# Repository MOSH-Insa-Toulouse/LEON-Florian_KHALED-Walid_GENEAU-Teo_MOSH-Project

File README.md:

___

# Keywords

___
> Arduino, Kicad, The Thing Networks, Lora, Node-Red, LT-spice  

___
# Membres du groupe

> Ce projet à été réalisé par : 
> - GENEAU Téo
> - KHALED Walid
> - LEON Florian
> 
___
# Description générale du projet 

Nous voulons dans ce projet réaliser un smart device, nous voulons récupérer les données d’un capteur de gaz et les envoyer via le protocole LORA sur le site TTN et ensuite afficher les données du capteur sur un Dashboard sur Node-Red. Nous nous intéressons aussi à la consommation d’Energie du capteur, donc nous allons utiliser le capteur sous un mode réveillé (très bref moment) pour mesurer et envoyer les données et un autre mode endormi où il ne consomme quasiment rien (pendant la majorité du temps).     

___
# Partie 1 : Conception du PCB 

Le Shield contient un circuit d’adaptation d’impédance pour relier le capteur de gaz au microcontrôleur (Arduino Uno) ainsi qu’un circuit d’interruption qui gère les deux mode «Sleep» et «Wake-up» du circuit et du capteur de gaz.

Un connecteur est prévu pour relier le circuit à l’antenne LORA. 

L’emplacement réservé au capteur de gaz est au milieu du PCB en forme de petits cercles. 

### **Schéma Kicad**

### **Visualisation du PCB** 

### **Visualisation du Shield en 3D** 

___
# Partie LT-SPICE 

Afin de simuler notre circuit d’interruption et gérer la consommation d’Energie du circuit nous avons utilisé LT-SPICE afin de simuler le comportement que nous désirons. 

Nous remarquons sur les deux figures suivantes qu’en variant les paramètres des différents composants du circuit notamment les résistances, nous parvenons à contrôler la durée d’interruption. 

___
# Partie Arduino 

Nous utilisons l’Arduino UNO comme microcontrôleur accompagné d’une breadboard pour monter le circuit prototype (circuit d’interruption + capteur de gaz groove + Antenne LORA). 

> Le code Arduino est composé des parties suivantes : 
>
> - Une partie d’acquisition des données du capteur et affichage sur moniteur série  
> - Une partie de configuration de la connexion TTN – LORA 
> - Une partie de gestion des deux modes Sleep et Wake-Up 

### **Affichage des données sur TTN** 

Les données sont envoyées sur le site TTN via LORA. 

Le code suivant nous permet de décoder les valeurs en hexadécimal reçues : 
```javascript
function decodeUplink(input) {
var data = input.bytes[0] << 8  | input.bytes[1];
  return {
    data: {
      gazValue: data/100
    },
    warnings: [],
    errors: []
  };
}
```

### **Partie consommation Energie**

Dans le but de diminuer au maximum la consommation d’Energie de notre système, nous avons utilisé un circuit d’interruption, nous arrivons même à éteindre et à rallumer le capteur avec ce circuit en rajoutant un transistor ce qui réduit énormément la consommation d’Energie du circuit car c’est le capteur qui consomme la quasi-totalité de l’Energie consommée par tout le circuit.

Ainsi, nous avons mis en place deux types d’interruption pour optimiser la consommation de notre circuit : une interruption matérielle et logicielle.

Notre interruption matérielle consiste en un déclenchement cyclique externe.

Pour cela, nous avons utilisé un AOP pour faire un comparateur, le circuit permet de généré des ondes carrées bases fréquences et de créer un circuit oscillateur permettant de faire varier la tension entre 0 et 5V de manière cyclique. Il est possible de modifier la fréquence en modifiant les valeurs de la capacité ou bien des résistances. En effet, si on augmente par exemple la valeur de la capacité, la fréquence diminuera et inversement. 

Nous avons simulé le circuit sur LT-Spice pour le choix des valeurs des résistances et de la capacité afin d’obtenir des périodes d’activités et d’inactivités adaptées à notre application.

L’interruption logicielle est réalisée par le code présent sur la carte. On réalise une interruption logicielle lorsque le circuit est dans une période inactive pour activer ou désactiver le capteur de gaz.

<ins>*Schéma du montage pour l’interruption logicielle (ici une LED à la place du capteur de gaz)*</ins>

Les figures suivantes montrent le comportement du système : 

L’interruption est annulée et le capteur se réveil «Wake-Up» prend la mesure et l’envoie (3 envoies pour éviter une potentiel perte du message) et se remet en mode «Sleep» pour s’en dormir. 

> «Dodo» (le capteur retourne au mode Sleep)
> 0 V en sortie de l’AOP 

> Mode Wake-Up et envoie de 3 messages (données)  
> 5 V en sortie de l’AOP

### **Bilan de puissance consommée**
Nous avons mesuré le courant en sortie du circuit, pour cela nous avons utilisé un détecteur d’intensité USB

<p style="text-align:center;"><ins><em>Détecteur de tension/intensité USB</em></ins></p>

Il permet de réaliser des mesures de courant consommé sur un port USB et ce en temps réel. Nous avons alors pu établir un tableau de mesures.

> Pour cela, nous avons mesurer la consommation en courant du circuit en fonction de son comportement :
> - En mode wake-up (actif), lorsque le circuit d’oscillation impose une tension à 5V.
> - En mode sleep, lorsque le circuit d’oscillation impose une tension à 0V et que le capteur de gaz est activé.
> - En mode sleep, lorsque le circuit d’oscillation impose une tension à 0V et que le capteur de gaz est désactivé par interruption logicielle.

Nous pouvons observer que c’est l’interruption matérielle qui a le plus d’impact sur la consommation, en effet, on passe de **0.22 à 0.04** A lors des périodes de sleep imposées par l’AOP comparateur, soit une réduction de **0.18 A**. Tandis que, l’interruption logicielle, elle, permet une économie de **0.16 A** en passant de **0.22 A à 0.06 A**, cette interruption permet de ne plus alimenter le capteur lors de la phase active, on peut alors remarquer que c’est le capteur de gaz qui consomme le plus dans le circuit avec une consommation correspond au **0.16 A** de différence. 

De plus, on a mesuré la durée des périodes de sleep et de wake-up du circuit, on observe une période moyenne de **123 secondes** pour les périodes inactives du circuit contre 17 secondes en moyenne pour la phase active, or, l’interruption logicielle active le capteur que pour une durée de **7 secondes**.

On convertit en heure et on multiplie par les valeurs de courant correspondantes mesurées pour obtenir la mesure en Ah, puis on multiplie par le voltage (5V) pour obtenir une mesure de puissance en Wh.

On a bien :
<!-- $$
P_{sleep} = \frac{123}{3600} \cdot 0.04 \cdot 5 = 6.833 \enspace mWh
$$ --> 

contre

<!-- $$
P_{actif} = \frac{7}{3600} \cdot 0.22 \cdot 5 = 2.138 \enspace mWh
$$ --> 

Soit P<sub>moy</sub> la puissance moyenne de notre système avec ce mécanisme sleep/wake-up.
<!-- $$
P_{moy} = \frac{P_{sleep} + P_{actif}}{2} = 4.4861 \enspace mWh
$$ --> 

Or, sans ce mécanisme on a bien une consommation de 0.22 A et 5 V pendant 140 s (123 + 17) soit :

<!-- $$
ConsoAmpere = \frac{140}{3600} \cdot 0.22 = 0.0085 \enspace Ah
$$ --> 

et 

<!-- $$
P_{max} = ConsoAmpere \cdot 5 = 42.77 \enspace mA
$$ --> 

On observe qu’on a quasiment divisé par 10 la consommation classique avec la mise en place de nos interruptions logicielles et matérielles.

<!-- $$
5V \cdot ah = Wh 
$$ --> 

---
# Partie Node-Red 
---
Afin d’afficher les données de notre capteur, Nous utilisons Node-Red, cela se fait en établissant une connexion via le protocole MQTT entre Node-Red et le site TTN. 

### **Paramétrage du nœud MQTT :** 

Des améliorations peuvent être faites comme par exemple afficher l’historique des valeurs de gaz pendant la journée ou bien pendant le mois…

Rajouter des boutons ou des sliders pour agir sur des actionneurs en down-link pour avertir par exemple via une alarme d’une valeur de gaz trop importante… 

___
___

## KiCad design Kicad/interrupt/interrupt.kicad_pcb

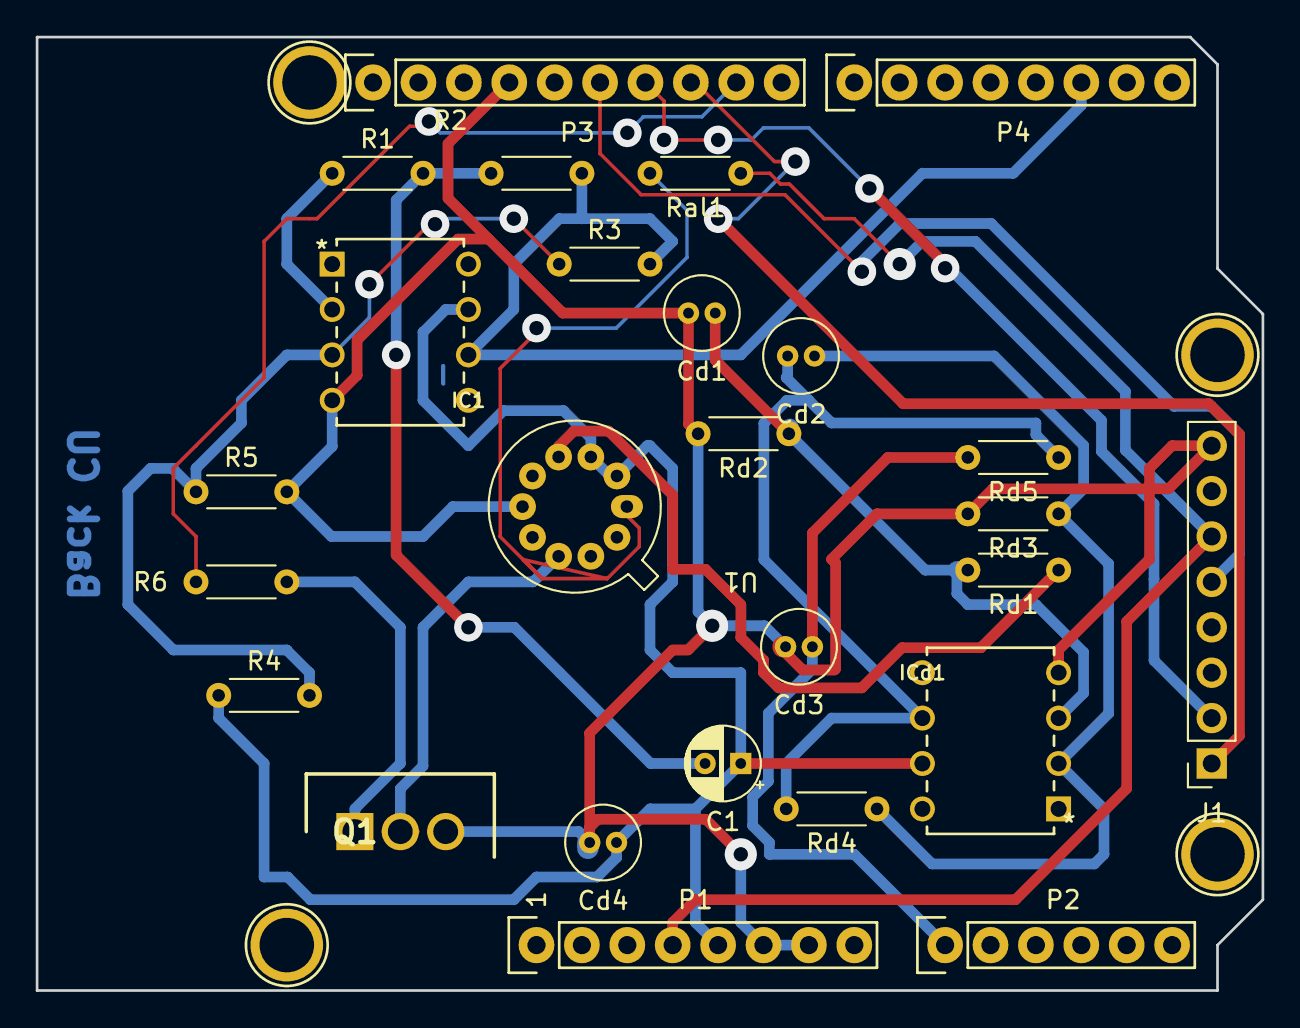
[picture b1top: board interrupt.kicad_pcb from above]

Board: 2 copper layers, 68.6 x 53.3 mm, 30 parts (0 on the bottom side), 21 nets.

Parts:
C1: C_Polarized; CP_Radial_D4.0mm_P2.00mm
Cd1, Cd3, Cd4: 100n; C_Radial_D4.0mm_H5.0mm_P1.50mm
Cd2: 1u; C_Radial_D4.0mm_H5.0mm_P1.50mm
IC1: LTC1050CS8#PBF; PDIP-8_N
ICd1: LTC1050CS8#PBF; PDIP-8_N
J1: Conn_LORA; PinSocket_1x08_P2.54mm_Vertical
P1: Power; Socket_Strip_Arduino_1x08
P2: Analog; Socket_Strip_Arduino_1x06
P3: Digital; Socket_Strip_Arduino_1x10
P4: Digital; Socket_Strip_Arduino_1x08
P5, P6, P7, P8: CONN_01X01; Arduino_1pin
Q1: IRF520; TO254P465X1024X2050-3P
R1, R2, R3, R4, R5, R6: 1M; R_Axial_DIN0204_L3.6mm_D1.6mm_P5.08mm_Horizontal
Ral1: R; R_Axial_DIN0204_L3.6mm_D1.6mm_P5.08mm_Horizontal
Rd1: 10k; R_Axial_DIN0204_L3.6mm_D1.6mm_P5.08mm_Horizontal
Rd2, Rd4: 100k; R_Axial_DIN0204_L3.6mm_D1.6mm_P5.08mm_Horizontal
Rd3, Rd5: 1k; R_Axial_DIN0204_L3.6mm_D1.6mm_P5.08mm_Horizontal
U1: GAZ_TO_5; GAZ_TO-5

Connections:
+3V3: J1.6, P1.4, Ral1.1
+5V: C1.1, Cd4.1, IC1.7 (V+), ICd1.7 (V+), P1.5, R4.1, U1.2 (R_Sens_1_IN), U1.3 (R_Poly_IN)
/A4(SDA): P2.5, P3.2
/A5(SCL): P2.6, P3.1
/DATA_Sensor: Cd3.1, P2.1, Rd5.2
/GATE: P3.9, R6.1
/GND_Gaz: Q1.2, U1.8 (R_Poly_OUT)
/RST: J1.5, P3.6
/RX: J1.2, P3.7
/TX: J1.1, P3.8
/VAOP: IC1.6 (OUT), P4.6, R2.1, R3.2
GND: Cd1.2, Cd3.2, Cd4.2, IC1.4 (V-), ICd1.4 (V-), J1.8, P1.6, P1.7, P3.4, Q1.3, R5.2, Rd2.2, Rd3.2, U1.6 (R_ALU_OUT)
unnamed: C1.2, R1.2, R2.2
unnamed: Cd1.1, ICd1.3 (+IN), Rd1.2, Rd2.1
unnamed: Cd2.1, ICd1.2 (-IN), Rd3.1, Rd4.1
unnamed: Cd2.2, ICd1.6 (OUT), Rd4.2, Rd5.1
unnamed: IC1.2 (-IN), R1.1
unnamed: IC1.3 (+IN), R3.1, R4.2, R5.1
unnamed: Q1.1, R6.2
unnamed: Ral1.2, U1.1 (R_ALU_IN)
unnamed: Rd1.1, U1.4 (R_Sens_1_OUT)

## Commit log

2021-11-18 Depot initial + code arduino TTN + node-red
2021-11-26 update code TTN
2021-11-26 photos montage
2021-11-26 Rajout bilan puissance
2021-11-26 simulation spice
    captures des simulations circuit d'interruptions
2021-11-26 fichier_kicad_circuit_interruption
    le fichier représente un shield qui se fixera sur arduino il aura deux emplacements pour fixer lora et capteur gaz ainsi que le circuit sleep
2021-11-30 TP_elec_analog
    fichiers de simulation circuit filtrage gaz sensor avec les résultats
2021-12-03 MODIF schéma
2021-12-06 modification schéma kicad
2022-01-12 new
    aef
2022-01-12 new
    new
2022-01-16 Création du readme
2022-01-16 update equations
2022-01-16 modification equation
2022-01-16 update photo quality
2022-01-26 Added gaz sensor Datasheet
